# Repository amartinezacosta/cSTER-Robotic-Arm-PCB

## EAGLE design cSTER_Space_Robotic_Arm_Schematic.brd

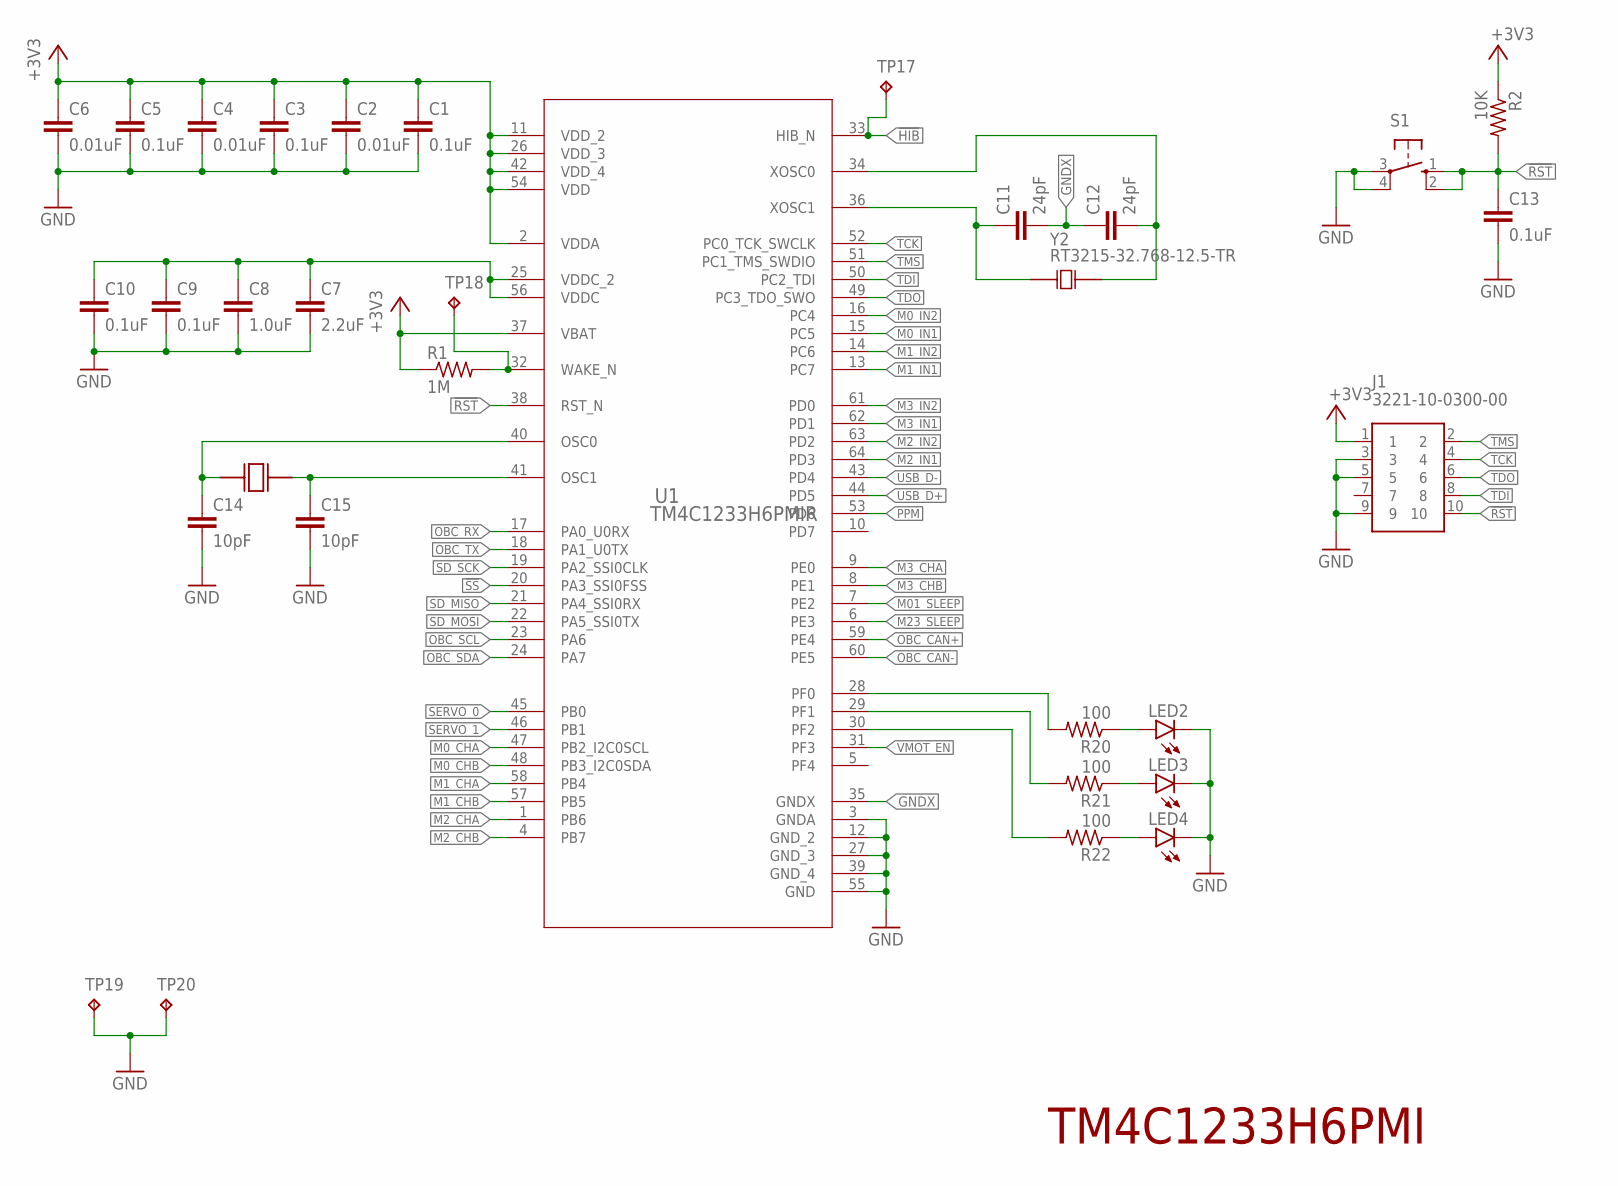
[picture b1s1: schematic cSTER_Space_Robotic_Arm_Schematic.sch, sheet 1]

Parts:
C1, C3, C5, C9, C10: 0.1uF; C0402K
C2, C4, C6: 0.01uF; C0402K
C7: 2.2uF; C0402K
C8: 1.0uF; C0402K
C11, C12: 24pF; C0402K
C13: 0.1uF; C0603
C14, C15: 10pF; C0402K
J1: 3221-10-0300-00
LED2, LED3, LED4: LEDCHIPLED_0805; CHIPLED_0805
R1: 1M; R0402
R2: 10K; R0603
R20, R21, R22: 100; R0603
S1: 10-XX; B3F-10XX
TP17, TP18, TP19, TP20: TPPAD1-13; P1-13
U1: TM4C1233H6PMIR; PM0064A_N
Y1: ECS-160-9-42-CKM-TR; XTAL_ECS-160-9-42-CKM-TR
Y2: RT3215-32.768-12.5-TR

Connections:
!HIB: TP17.TP, U1.33 (HIB_N)
!RST: C13.1, J1.10, R2.2, S1.1 (S), S1.2 (S1), U1.38 (RST_N)
!SS: U1.20 (PA3_SSI0FSS); also elsewhere on the board
+3V3: C1.1, C2.1, C3.1, C4.1, C5.1, C6.1, J1.1, R1.1, R2.1, U1.2 (VDDA), U1.11 (VDD_2), U1.26 (VDD_3), U1.37 (VBAT), U1.42 (VDD_4), U1.54 (VDD); also elsewhere on the board
GND: C1.2, C2.2, C3.2, C4.2, C5.2, C6.2, C7.2, C8.2, C9.2, C10.2, C13.2, C14.2, C15.2, J1.3, J1.5, J1.9, LED2.C, LED3.C, LED4.C, S1.3, S1.4 (P1), TP19.TP, TP20.TP, U1.3 (GNDA), U1.12 (GND_2), U1.27 (GND_3), U1.39 (GND_4), U1.55 (GND); also elsewhere on the board
GNDX: C11.2, C12.1, U1.35 (GNDX)
M0_CHA: U1.47 (PB2_I2C0SCL); also elsewhere on the board
M0_CHB: U1.48 (PB3_I2C0SDA); also elsewhere on the board
M0_IN1: U1.15 (PC5); also elsewhere on the board
M0_IN2: U1.16 (PC4); also elsewhere on the board
M1_CHA: U1.58 (PB4); also elsewhere on the board
M1_CHB: U1.57 (PB5); also elsewhere on the board
M1_IN1: U1.13 (PC7); also elsewhere on the board
M1_IN2: U1.14 (PC6); also elsewhere on the board
M01_SLEEP: U1.7 (PE2); also elsewhere on the board
M2_CHA: U1.1 (PB6); also elsewhere on the board
M2_CHB: U1.4 (PB7); also elsewhere on the board
M2_IN1: U1.64 (PD3); also elsewhere on the board
M2_IN2: U1.63 (PD2); also elsewhere on the board
M3_CHA: U1.9 (PE0); also elsewhere on the board
M3_CHB: U1.8 (PE1); also elsewhere on the board
M3_IN1: U1.62 (PD1); also elsewhere on the board
M3_IN2: U1.61 (PD0); also elsewhere on the board
M23_SLEEP: U1.6 (PE3); also elsewhere on the board
unnamed: C11.1, U1.36 (XOSC1), Y2.1
unnamed: C14.1, U1.40 (OSC0), Y1.1
unnamed: C12.2, U1.34 (XOSC0), Y2.2
unnamed: R1.2, TP18.TP, U1.32 (WAKE_N)
unnamed: C7.1, C8.1, C9.1, C10.1, U1.25 (VDDC_2), U1.56 (VDDC)
unnamed: C15.1, U1.41 (OSC1), Y1.3 (2)
unnamed: LED2.A, R20.1
unnamed: LED3.A, R21.1
unnamed: LED4.A, R22.1
unnamed: R20.2, U1.28 (PF0)
unnamed: R21.2, U1.29 (PF1)
unnamed: R22.2, U1.30 (PF2)
OBC_CAN+: U1.59 (PE4); also elsewhere on the board
OBC_CAN-: U1.60 (PE5); also elsewhere on the board
OBC_RX: U1.17 (PA0_U0RX); also elsewhere on the board
OBC_SCL: U1.23 (PA6); also elsewhere on the board
OBC_SDA: U1.24 (PA7); also elsewhere on the board
OBC_TX: U1.18 (PA1_U0TX); also elsewhere on the board
PPM: U1.53 (PD6); also elsewhere on the board
SD_MISO: U1.21 (PA4_SSI0RX); also elsewhere on the board
SD_MOSI: U1.22 (PA5_SSI0TX); also elsewhere on the board
SD_SCK: U1.19 (PA2_SSI0CLK); also elsewhere on the board
SERVO_0: U1.45 (PB0); also elsewhere on the board
SERVO_1: U1.46 (PB1); also elsewhere on the board
TCK: J1.4, U1.52 (PC0_TCK_SWCLK)
TDI: J1.8, U1.50 (PC2_TDI)
TDO: J1.6, U1.49 (PC3_TDO_SWO)
TMS: J1.2, U1.51 (PC1_TMS_SWDIO)
USB_D+: U1.44 (PD5); also elsewhere on the board
USB_D-: U1.43 (PD4); also elsewhere on the board
VMOT_EN: U1.31 (PF3); also elsewhere on the board

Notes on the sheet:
TM4C1233H6PMI

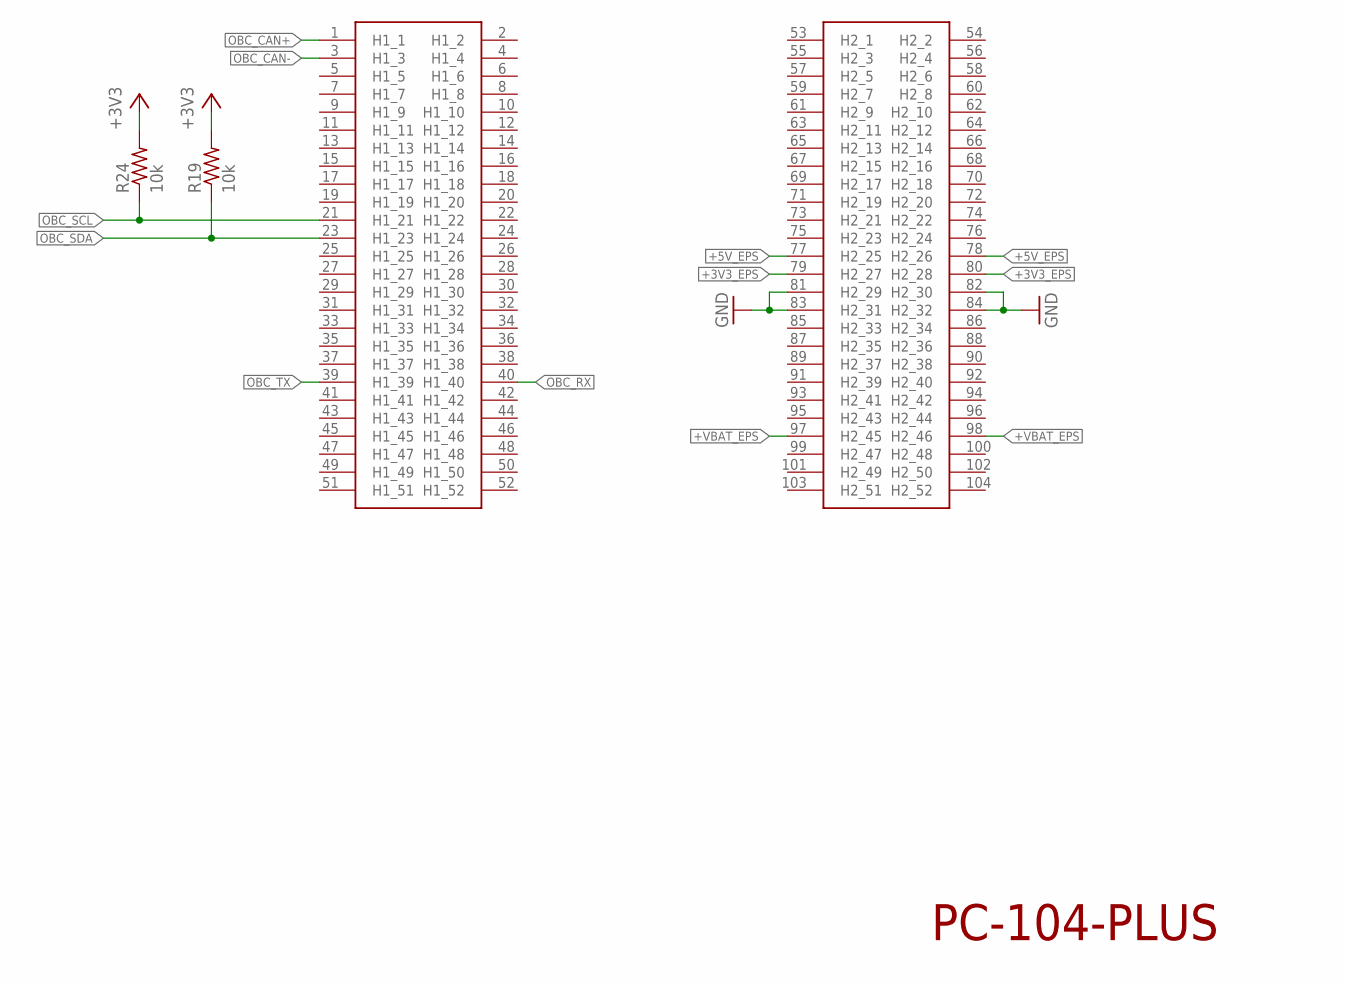
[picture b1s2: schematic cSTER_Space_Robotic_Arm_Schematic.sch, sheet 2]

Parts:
J2: PC-104-PLUS
R19, R24: 10k; R0603

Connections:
+3V3: R19.2, R24.2; also elsewhere on the board
+3V3_EPS: J2.79 (H2_27), J2.80 (H2_28); also elsewhere on the board
+5V_EPS: J2.77 (H2_25), J2.78 (H2_26); also elsewhere on the board
+VBAT_EPS: J2.97 (H2_45), J2.98 (H2_46); also elsewhere on the board
GND: J2.81 (H2_29), J2.82 (H2_30), J2.83 (H2_31), J2.84 (H2_32); also elsewhere on the board
OBC_CAN+: J2.1 (H1_1); also elsewhere on the board
OBC_CAN-: J2.3 (H1_3); also elsewhere on the board
OBC_RX: J2.40 (H1_40); also elsewhere on the board
OBC_SCL: J2.21 (H1_21), R24.1; also elsewhere on the board
OBC_SDA: J2.23 (H1_23), R19.1; also elsewhere on the board
OBC_TX: J2.39 (H1_39); also elsewhere on the board

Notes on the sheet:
PC-104-PLUS

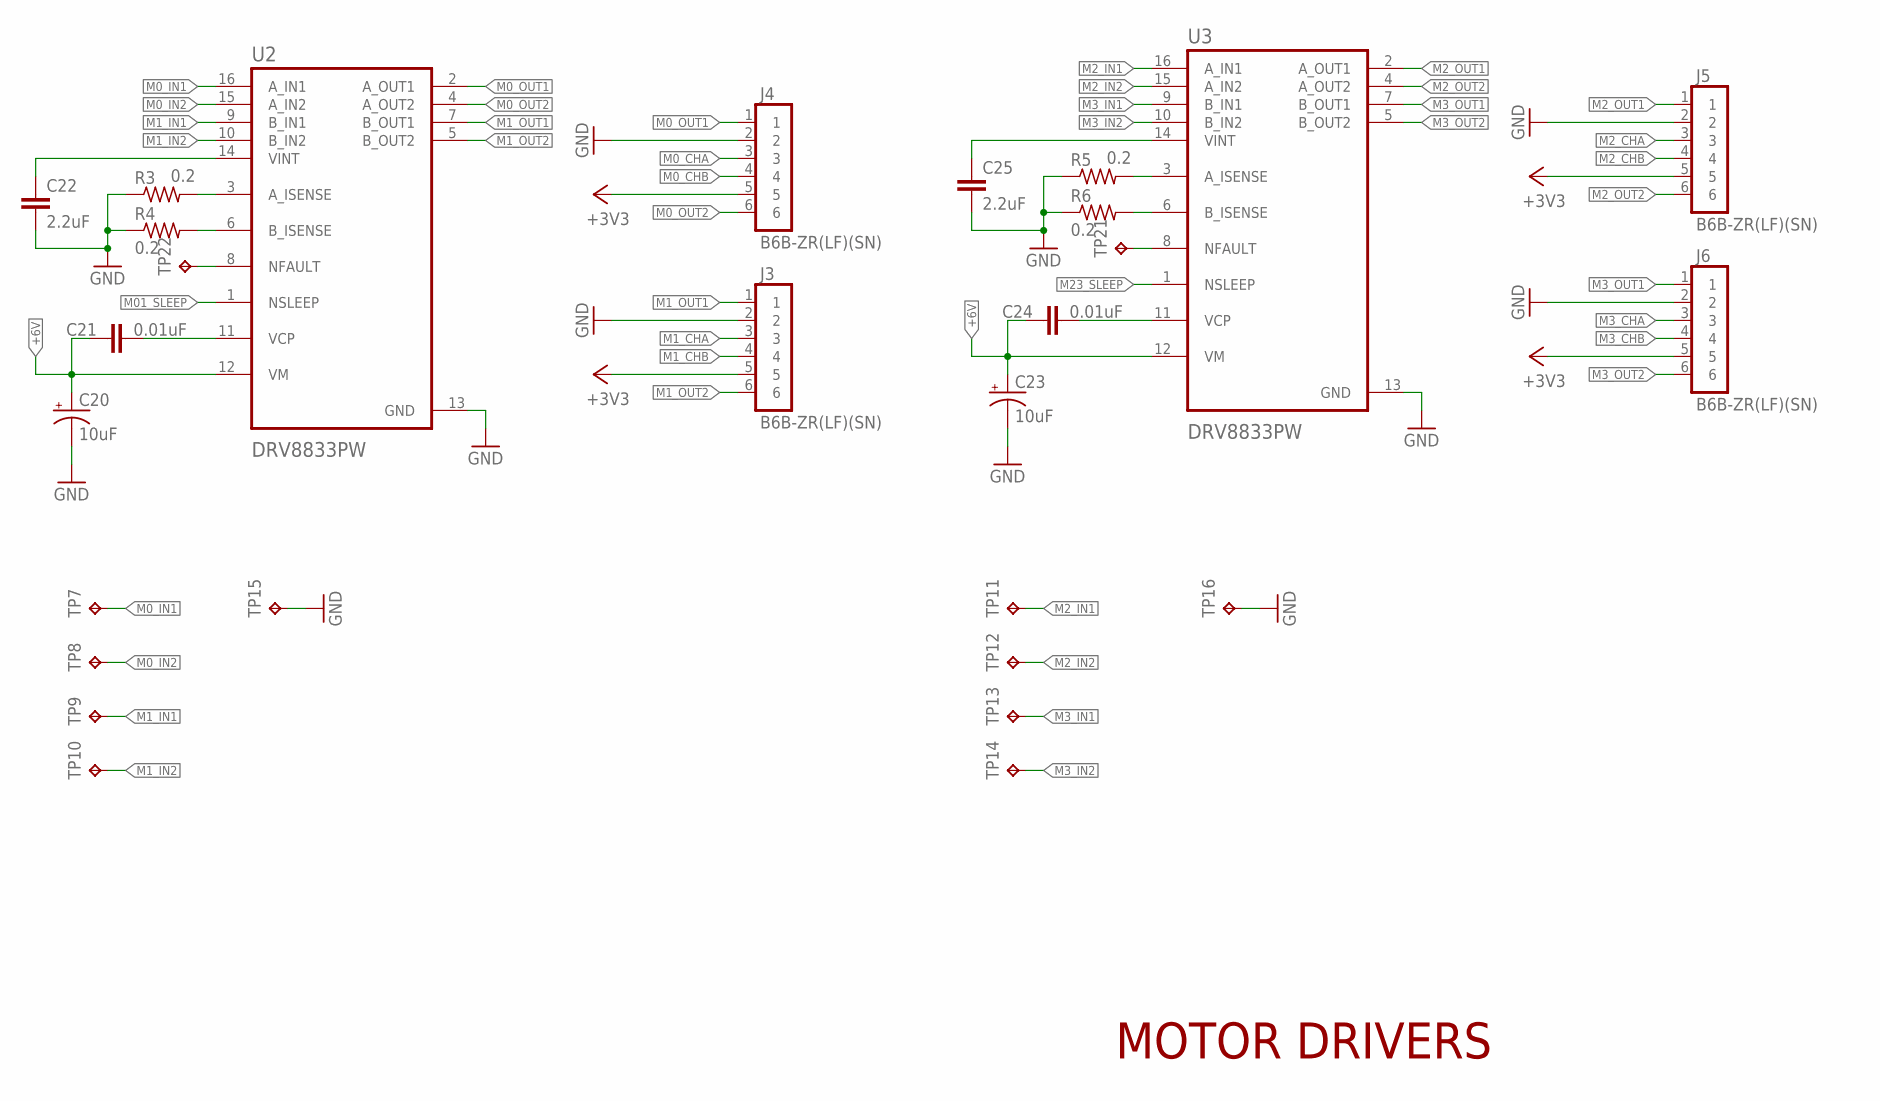
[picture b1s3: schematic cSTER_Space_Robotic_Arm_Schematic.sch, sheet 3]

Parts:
C20, C23: 10uF; CT3216
C21, C24: 0.01uF; C0805
C22, C25: 2.2uF; C0603
J3, J4, J5, J6: B6B-ZR(LF)(SN); JST_B6B-ZR(LF)(SN)
R3, R4, R5, R6: 0.2; R1206
TP7, TP8, TP9, TP10, TP11, TP12, TP13, TP14, TP15, TP16, TP21, TP22: TPPAD1-13; P1-13
U2, U3: DRV8833PW; SOP65P640X120-16N

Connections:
+3V3: J3.5, J4.5, J5.5, J6.5; also elsewhere on the board
+6V: C20.+, C21.1, C23.+, C24.1, U2.12 (VM), U3.12 (VM); also elsewhere on the board
GND: C20.-, C22.2, C23.-, C25.2, J3.2, J4.2, J5.2, J6.2, R3.1, R4.1, R5.1, R6.1, TP15.TP, TP16.TP, U2.13 (GND), U3.13 (GND); also elsewhere on the board
M0_CHA: J4.3; also elsewhere on the board
M0_CHB: J4.4; also elsewhere on the board
M0_IN1: TP7.TP, U2.16 (A_IN1); also elsewhere on the board
M0_IN2: TP8.TP, U2.15 (A_IN2); also elsewhere on the board
M0_OUT1: J4.1, U2.2 (A_OUT1)
M0_OUT2: J4.6, U2.4 (A_OUT2)
M1_CHA: J3.3; also elsewhere on the board
M1_CHB: J3.4; also elsewhere on the board
M1_IN1: TP9.TP, U2.9 (B_IN1); also elsewhere on the board
M1_IN2: TP10.TP, U2.10 (B_IN2); also elsewhere on the board
M1_OUT1: J3.1, U2.7 (B_OUT1)
M1_OUT2: J3.6, U2.5 (B_OUT2)
M01_SLEEP: U2.1 (NSLEEP); also elsewhere on the board
M2_CHA: J5.3; also elsewhere on the board
M2_CHB: J5.4; also elsewhere on the board
M2_IN1: TP11.TP, U3.16 (A_IN1); also elsewhere on the board
M2_IN2: TP12.TP, U3.15 (A_IN2); also elsewhere on the board
M2_OUT1: J5.1, U3.2 (A_OUT1)
M2_OUT2: J5.6, U3.4 (A_OUT2)
M3_CHA: J6.3; also elsewhere on the board
M3_CHB: J6.4; also elsewhere on the board
M3_IN1: TP13.TP, U3.9 (B_IN1); also elsewhere on the board
M3_IN2: TP14.TP, U3.10 (B_IN2); also elsewhere on the board
M3_OUT1: J6.1, U3.7 (B_OUT1)
M3_OUT2: J6.6, U3.5 (B_OUT2)
M23_SLEEP: U3.1 (NSLEEP); also elsewhere on the board
unnamed: R3.2, U2.3 (A_ISENSE)
unnamed: R4.2, U2.6 (B_ISENSE)
unnamed: C21.2, U2.11 (VCP)
unnamed: C22.1, U2.14 (VINT)
unnamed: R5.2, U3.3 (A_ISENSE)
unnamed: R6.2, U3.6 (B_ISENSE)
unnamed: C24.2, U3.11 (VCP)
unnamed: TP21.TP, U3.8 (NFAULT)
unnamed: C25.1, U3.14 (VINT)
unnamed: TP22.TP, U2.8 (NFAULT)

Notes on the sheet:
MOTOR DRIVERS

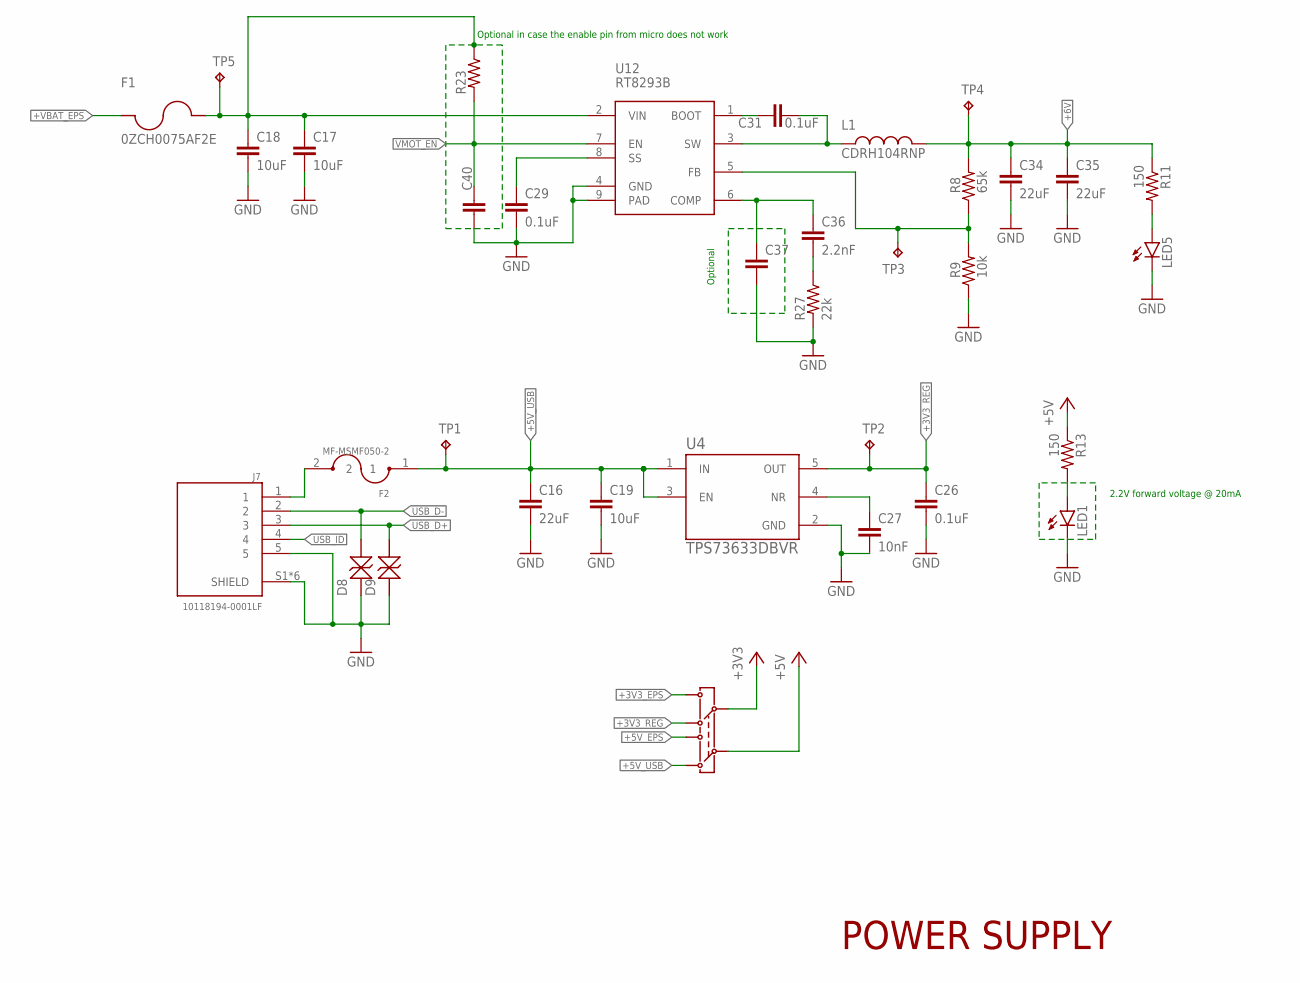
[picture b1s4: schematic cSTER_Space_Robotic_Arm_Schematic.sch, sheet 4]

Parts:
C16, C34, C35: 22uF; C1206
C17, C18: 10uF; C1206
C19: 10uF; C0603
C26, C29, C31: 0.1uF; C0603
C27: 10nF; C0603
C36: 2.2nF; C0603
C37, C40: C-EUC0603; C0603
D8, D9: CPDQC5V0R
F1: 0ZCH0075AF2E
F2: MF-MSMF050-2; FUSM4632X85
J7: 10118194-0001LF; AMPHENOL_10118194-0001LF
L1: CDRH104RNP
LED1, LED5: LEDCHIPLED_0805; CHIPLED_0805
R8: 65k; R0603
R9: 10k; R0603
R11, R13: 150; R0603
R23: R-US_R0603; R0603
R27: 22k; R0603
TP1, TP2, TP3, TP4, TP5: TPPAD1-13; P1-13
U4: TPS73633DBVR; SOT95P280X145-5N
U12: RT8293B
U$1: JS202011CQN

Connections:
+3V3: U$1.5; also elsewhere on the board
+3V3_EPS: U$1.6; also elsewhere on the board
+3V3_REG: C26.1, TP2.TP, U4.5 (OUT), U$1.4
+5V: R13.1, U$1.2; also elsewhere on the board
+5V_EPS: U$1.3; also elsewhere on the board
+5V_USB: C16.1, C19.1, F2.1, TP1.TP, U4.1 (IN), U4.3 (EN), U$1.1
+6V: C34.1, C35.1, L1.2, R8.2, R11.1, TP4.TP; also elsewhere on the board
+VBAT_EPS: F1.1; also elsewhere on the board
GND: C16.2, C17.2, C18.2, C19.2, C26.2, C27.2, C29.2, C34.2, C35.2, C37.2, C40.1, D8.1, D9.1, J7.5, J7.S1 (SHIELD), J7.S2 (SHIELD), J7.S3 (SHIELD), J7.S4 (SHIELD), J7.S5 (SHIELD), J7.S6 (SHIELD), LED1.C, LED5.C, R9.1, R27.2, U4.2 (GND), U12.4 (GND), U12.9 (PAD); also elsewhere on the board
unnamed: F2.2, J7.1
unnamed: C31.1, U12.1 (BOOT)
unnamed: C27.1, U4.4 (NR)
unnamed: C29.1, U12.8 (SS)
unnamed: LED1.A, R13.2
unnamed: LED5.A, R11.2
unnamed: C31.2, L1.1, U12.3 (SW)
unnamed: R8.1, R9.2, TP3.TP, U12.5 (FB)
unnamed: C36.1, C37.1, U12.6 (COMP)
unnamed: C36.2, R27.1
unnamed: C17.1, C18.1, F1.2, R23.1, TP5.TP, U12.2 (VIN)
USB_D+: D9.2, J7.3; also elsewhere on the board
USB_D-: D8.2, J7.2; also elsewhere on the board
USB_ID: J7.4
VMOT_EN: C40.2, R23.2, U12.7 (EN); also elsewhere on the board

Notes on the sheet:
POWER SUPPLY
2.2V forward voltage @ 20mA
Optional
Optional in case the enable pin from micro does not work

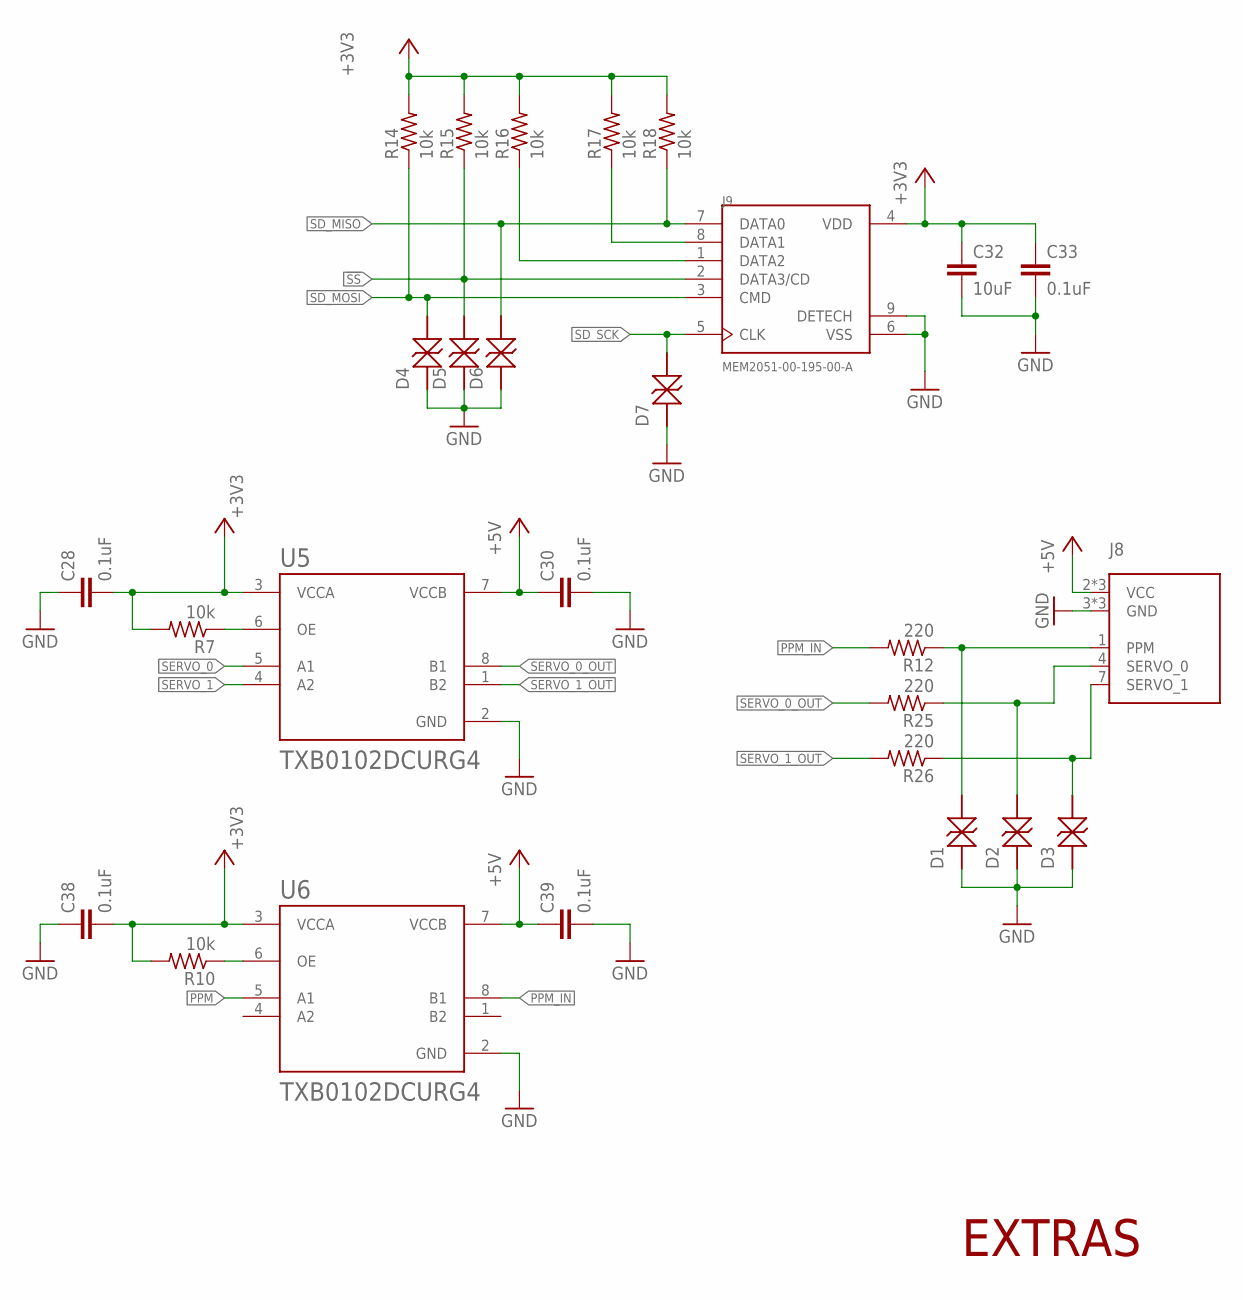
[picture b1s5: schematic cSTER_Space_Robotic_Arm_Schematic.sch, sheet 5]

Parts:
C28, C30, C38, C39: 0.1uF; C0402K
C32: 10uF; C0603
C33: 0.1uF; C0603
D1, D2, D3, D4, D5, D6, D7: CPDQC5V0R
J8: ROBOT_PORT
J9: MEM2051-00-195-00-A; GCT_MEM2051-00-195-00-A
R7, R10: 10k; R0402
R12, R25, R26: 220; R0603
R14, R15, R16, R17, R18: 10k; R0603
U5, U6: TXB0102DCURG4; SOP50P310X90-8N

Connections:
!SS: D5.2, J9.2 (DATA3/CD), R15.1; also elsewhere on the board
+3V3: C28.2, C32.1, C33.1, C38.2, J9.4 (VDD), R7.2, R10.2, R14.2, R15.2, R16.2, R17.2, R18.2, U5.3 (VCCA), U6.3 (VCCA); also elsewhere on the board
+5V: C30.1, C39.1, J8.2 (VCC), J8.5 (VCC), J8.8 (VCC), U5.7 (VCCB), U6.7 (VCCB); also elsewhere on the board
GND: C28.1, C30.2, C32.2, C33.2, C38.1, C39.2, D1.1, D2.1, D3.1, D4.1, D5.1, D6.1, D7.1, J8.3 (GND), J8.6 (GND), J8.9 (GND), J9.6 (VSS), J9.9 (DETECH), U5.2 (GND), U6.2 (GND); also elsewhere on the board
unnamed: R7.1, U5.6 (OE)
unnamed: D3.2, J8.7 (SERVO_1), R26.1
unnamed: J9.8 (DATA1), R17.1
unnamed: J9.1 (DATA2), R16.1
unnamed: D2.2, J8.4 (SERVO_0), R25.1
unnamed: R10.1, U6.6 (OE)
unnamed: D1.2, J8.1 (PPM), R12.1
PPM: U6.5 (A1); also elsewhere on the board
PPM_IN: R12.2, U6.8 (B1)
SD_MISO: D6.2, J9.7 (DATA0), R18.1; also elsewhere on the board
SD_MOSI: D4.2, J9.3 (CMD), R14.1; also elsewhere on the board
SD_SCK: D7.2, J9.5 (CLK); also elsewhere on the board
SERVO_0: U5.5 (A1); also elsewhere on the board
SERVO_0_OUT: R25.2, U5.8 (B1)
SERVO_1: U5.4 (A2); also elsewhere on the board
SERVO_1_OUT: R26.2, U5.1 (B2)

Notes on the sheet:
EXTRAS

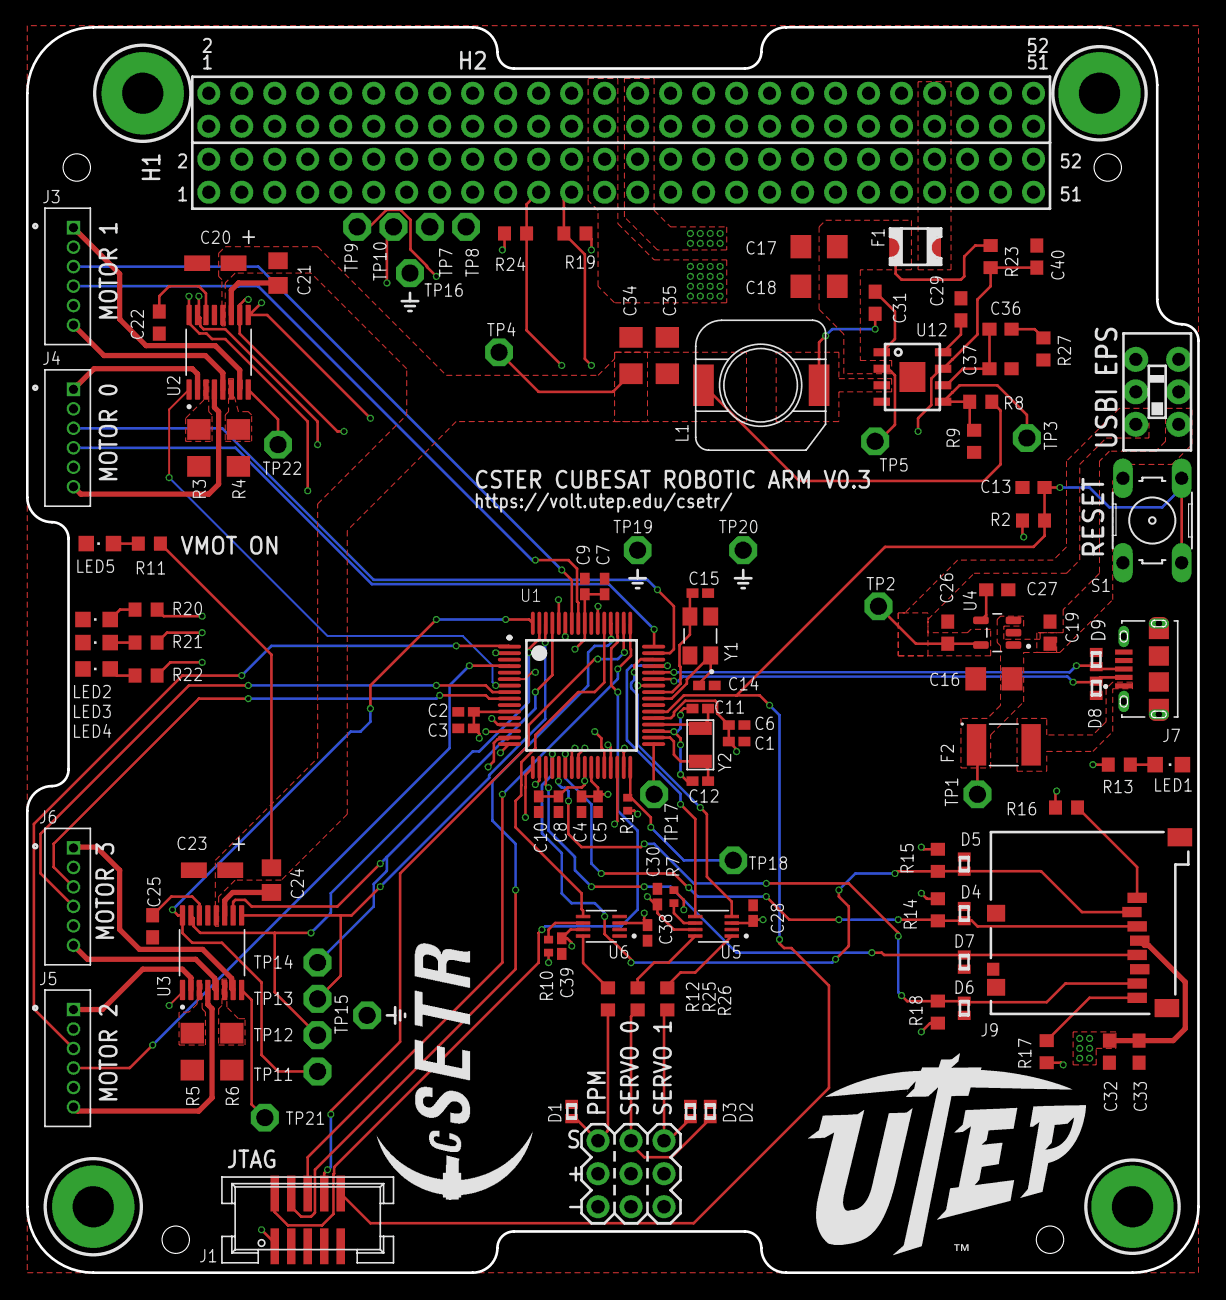
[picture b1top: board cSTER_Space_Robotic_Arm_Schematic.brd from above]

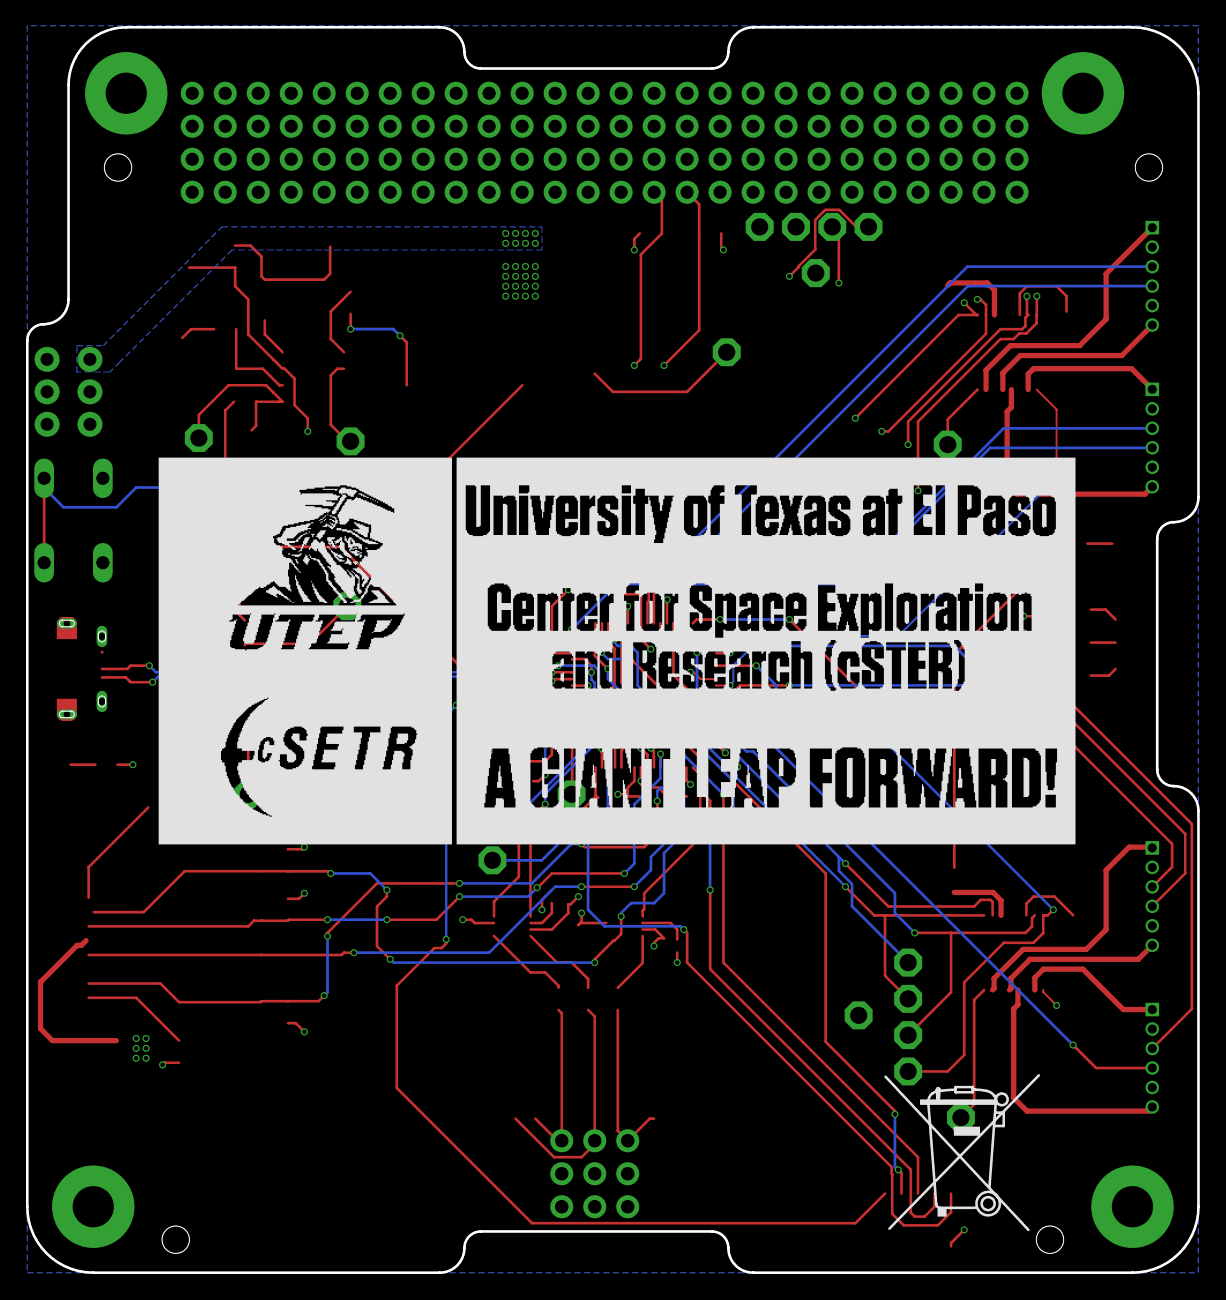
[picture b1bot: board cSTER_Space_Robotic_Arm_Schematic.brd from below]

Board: 4 copper layers, 90.2 x 95.9 mm, 133 parts (2 on the bottom side), 101 nets.

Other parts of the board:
U$4: CSTER
U$5: UTEP_LOGO
U$7: CSTER_UTEP_LOGO
U$8: MUELLTONNE
U$10, U$11, U$13, U$14: GND

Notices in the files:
parts and their libraries:
COPYRIGHT: Copyright (C) 2021 Ultra Librarian. All rights reserved.
